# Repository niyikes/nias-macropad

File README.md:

# nias-macropad

this hackpad features 6 keys, a rotary encoder and an OLED display, and uses KMK firmware.

this is my first hardware project and it was SO MUCH FUN i literally couldn't stop and speedran the whole thing in two days. like i'm talking morning to night completely locked in.

would do it again 10/10

fusion 360 was really annoying to figure out. measuring everything to fit together properly took FOREVER.

making the PCB was actually fun though. routing traces felt like playing a game haha.

the hackclub slack was REALLY helpful even though I was just lurking the entire time :D

i think i'm also going to paint the top case later!

## Specifications:
- XIAO RP2040 brain
- 128x32 OLED Display
- 1 EC11 Rotary encoder
- 6 keys

### PCB & Schematics

<table>
<tr>
<td width="50%">

</td>
<td width="50%">

</td>
</tr>
<tr>
<td align="center"><b>PCB</b></td>
<td align="center"><b>Schematics</b></td>
</tr>
</table>

## Firmware:
The whole thing runs on KMK firmware.

The rotary encoder is a volume knob, press it to pause/play.

The 6 keys are mapped to everyday shortcuts:
- Ctrl+Z (Undo)
- Ctrl+Y (Redo)
- Ctrl+C (Copy)
- Ctrl+V (Paste)
- Alt+Tab (Switch windows)
- Ctrl+Tab (Switch tabs)

I don't know what to make the OLED display just yet, so it has some random text for now.

I'm planning on making the entire thing more interesting later...

## BOM:
- 1x Seeed XIAO RP2040 (Microcontroller)
- 6x Cherry MX switches
- 6x Compatible Keycaps
- 1x EC11 Rotary encoder with push button
- 1x Rotary encoder knob
- 1x SSD1306 OLED display (128x32, I2C)
- 1x Custom PCB
- 3D printed top plate & bottom case (preferred color: pastel blue, or any other pastel color) 
- 4x M3 bolts & heatset inserts
- 4x M3 bolts & heatset inserts

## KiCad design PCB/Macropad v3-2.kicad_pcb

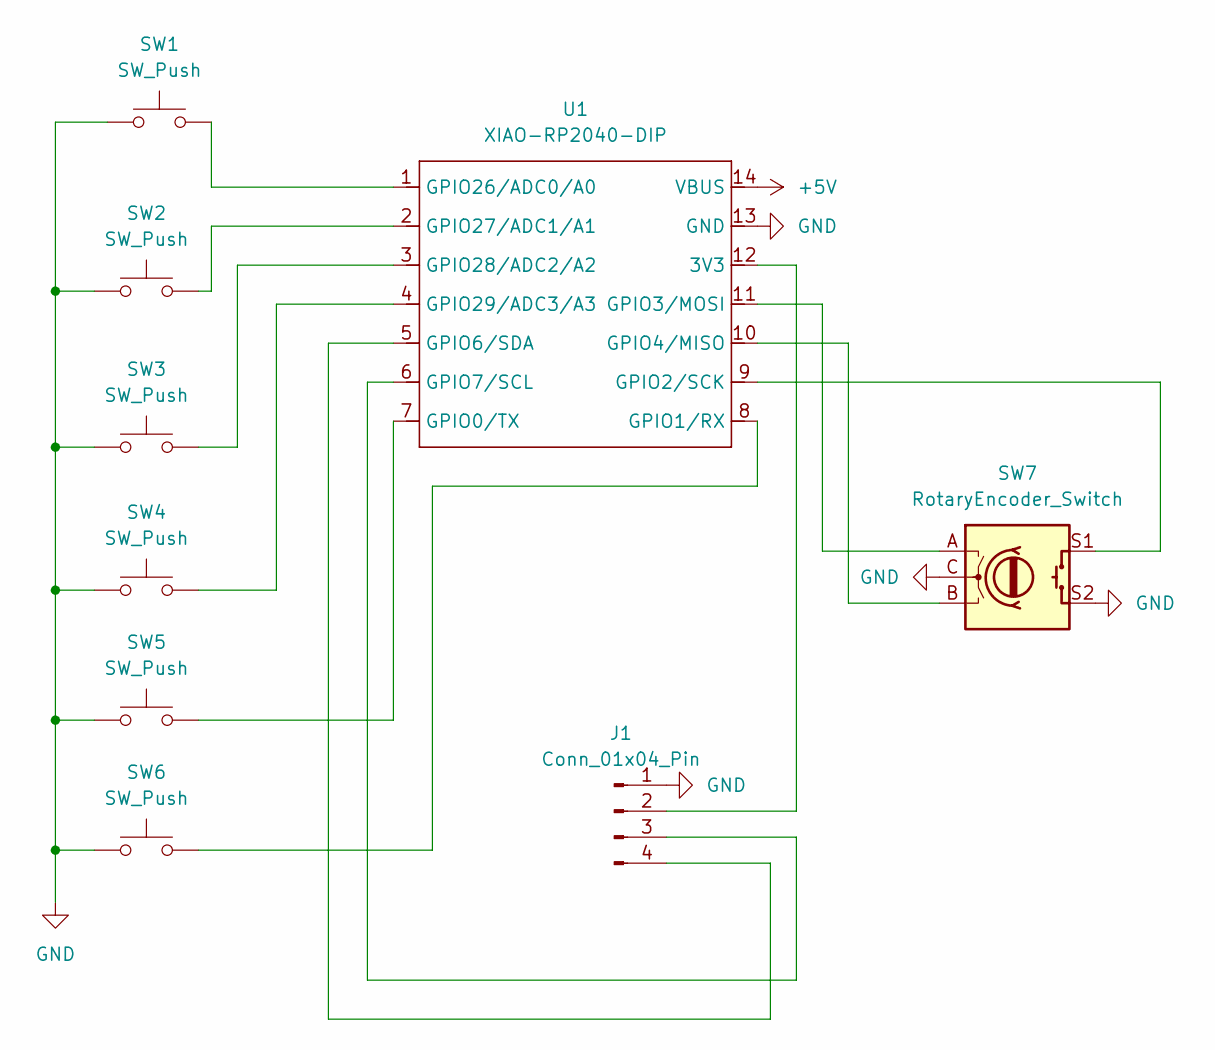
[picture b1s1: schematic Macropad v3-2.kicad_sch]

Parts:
J1: Conn_01x04_Pin; SSD1306-0.91-OLED-4pin-128x32
SW1, SW2, SW3, SW4, SW5, SW6: SW_Push; SW_Cherry_MX_1.00u_PCB
SW7: RotaryEncoder_Switch; RotaryEncoder_Alps_EC11E-Switch_Vertical_H20mm
U1: XIAO-RP2040-DIP

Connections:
+5V: U1.14 (VBUS)
GND: J1.1, SW1.1, SW2.1, SW3.1, SW4.1, SW5.1, SW6.1, SW7.C, SW7.S2, U1.13 (GND)
unnamed: J1.2, U1.12 (3V3)
unnamed: J1.3, U1.6 (GPIO7/SCL)
unnamed: J1.4, U1.5 (GPIO6/SDA)
unnamed: SW5.2, U1.7 (GPIO0/TX)
unnamed: SW6.2, U1.8 (GPIO1/RX)
unnamed: SW7.S1, U1.9 (GPIO2/SCK)
unnamed: SW7.A, U1.11 (GPIO3/MOSI)
unnamed: SW7.B, U1.10 (GPIO4/MISO)
unnamed: SW1.2, U1.1 (GPIO26/ADC0/A0)
unnamed: SW2.2, U1.2 (GPIO27/ADC1/A1)
unnamed: SW3.2, U1.3 (GPIO28/ADC2/A2)
unnamed: SW4.2, U1.4 (GPIO29/ADC3/A3)

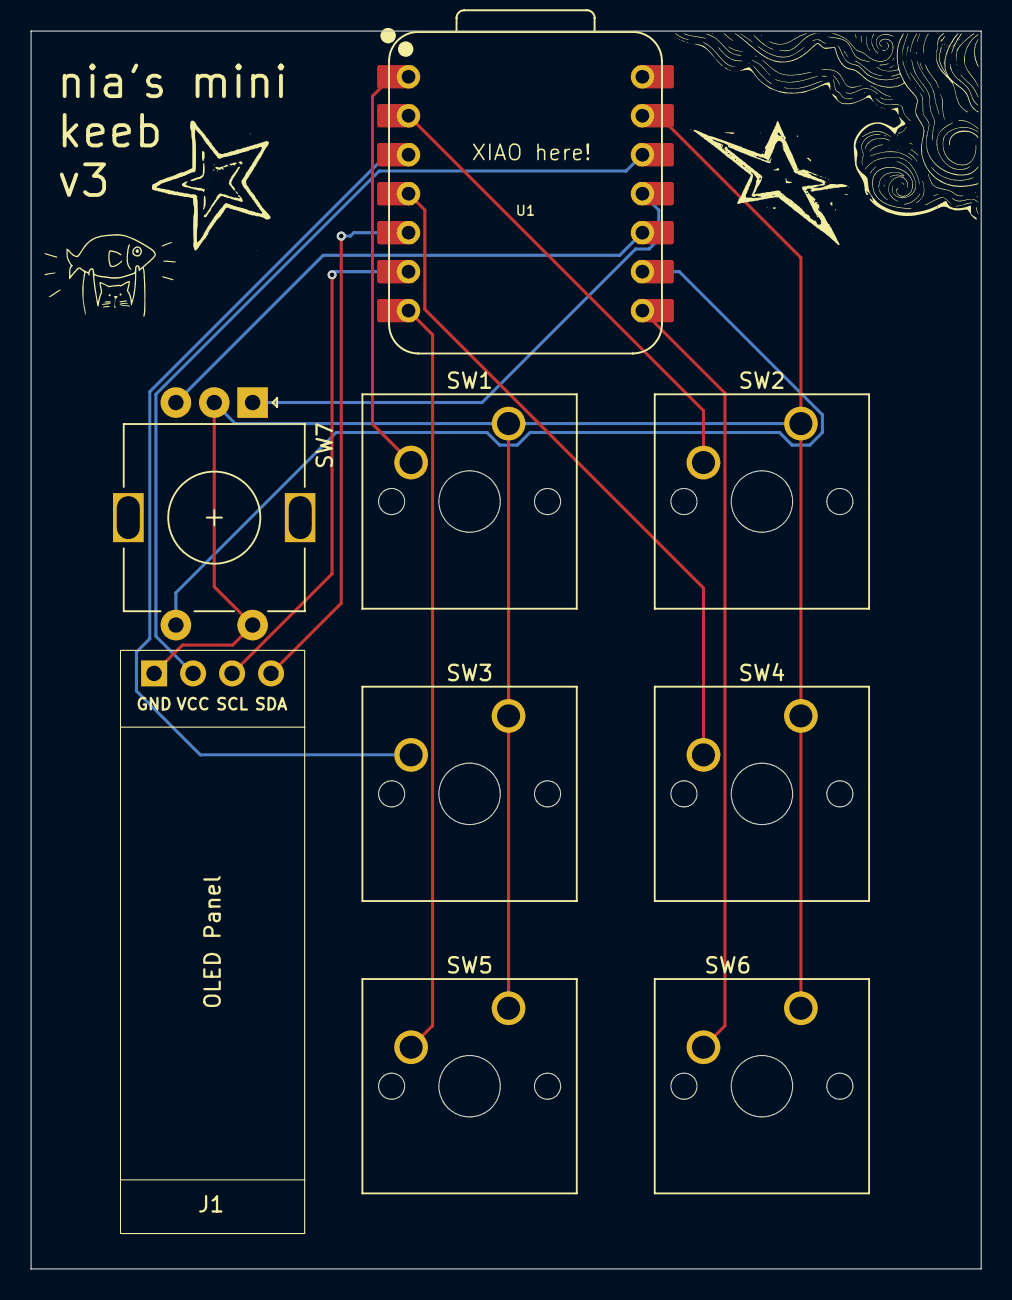
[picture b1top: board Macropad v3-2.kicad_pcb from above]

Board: 2 copper layers, 61.9 x 80.7 mm, 9 parts (0 on the bottom side), 13 nets.

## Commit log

2026-01-16 Update README.md
    fixed schematics and PCB
2026-01-16 Fixed Schematics
2026-01-17 Update README.md
    Updated Schematics and PCB
2026-01-17 Update Schematics and Case
